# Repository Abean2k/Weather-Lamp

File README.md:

# Weather-Lamp

A lamp with 5 RGB LED's that connects to the weather usign ESP32 to display the "mood" outside. Made for STASIS. 

## Assembly Guide
### Items you need (Besides the PCB and 3D Printed Parts):
2 M3 6mm-12mm screws
2 M4 6mm-12mm screws

First take the base and slide in the oled screen. Keep the wires up like in the picture so that they line up with the cutout in the base. 

Next use the 2 M3 screws to screw the base to the PCB. Make sure to keep the usb on the esp 32 facing the cutout. Also keep LEDs up.

Then prepare the top cover by glueing the the translusent petg crystle to the lip of the top cover usign super glue or hotglue. Be careful while handeling the crystle as 1 layered 3d prints are fragile. 

Finally, take the top cover with the crystle on it and screw it into the base with the 2 M4 screws. 

That's it, now just ubload firmware and you are good to go :)

## Design:
I wanted this lamp to be small and unique. This is why I choose to make a more difficult, but better looking crystal/geode lamp. I also wanted to have an OLED to convey the exact temperature which was something the rgb lamp could not. For the base of the design I tried to keep it as minimalist as possible, which led to it essentially wrapping around the circular pcb, with a flat front surface for the oled. 

The bottom two peices; bottom case, and top cover will be printed using pla in gray or black and the crystle will be a vase mode print with clear/transulcent PETG. PCB will be assembled by hand.  

## PCB:
I made my 2 layered pcb for this project on kicad. I choose to use a pcb for this project in order to keep the lamp internals neat and professional looking. The design of this pcb keeps the LEDs in a circle with one in the center and the microcontroller and capacitor on the back side. For the OLED a header allows me to connect and solder the wires to the pcb to the OLED while allowing the OLED to be in a different direction from my LEDs and microcontroller.

### Schematic

### PCB Layout

## Firmware:
The firmware for this project was made in arduino in c++. It tells the microcontroller how to fetch data from OpenWeather and use the temperature and weather code data from that to light up the LEDs and display the temperature on the OLED in fahrenheit. 

#### How to Upload: Plug in usb through the large opening and upload through arudino ide.

## BOM:

Note: For items with more than my reqired amount it is due to min order limits.

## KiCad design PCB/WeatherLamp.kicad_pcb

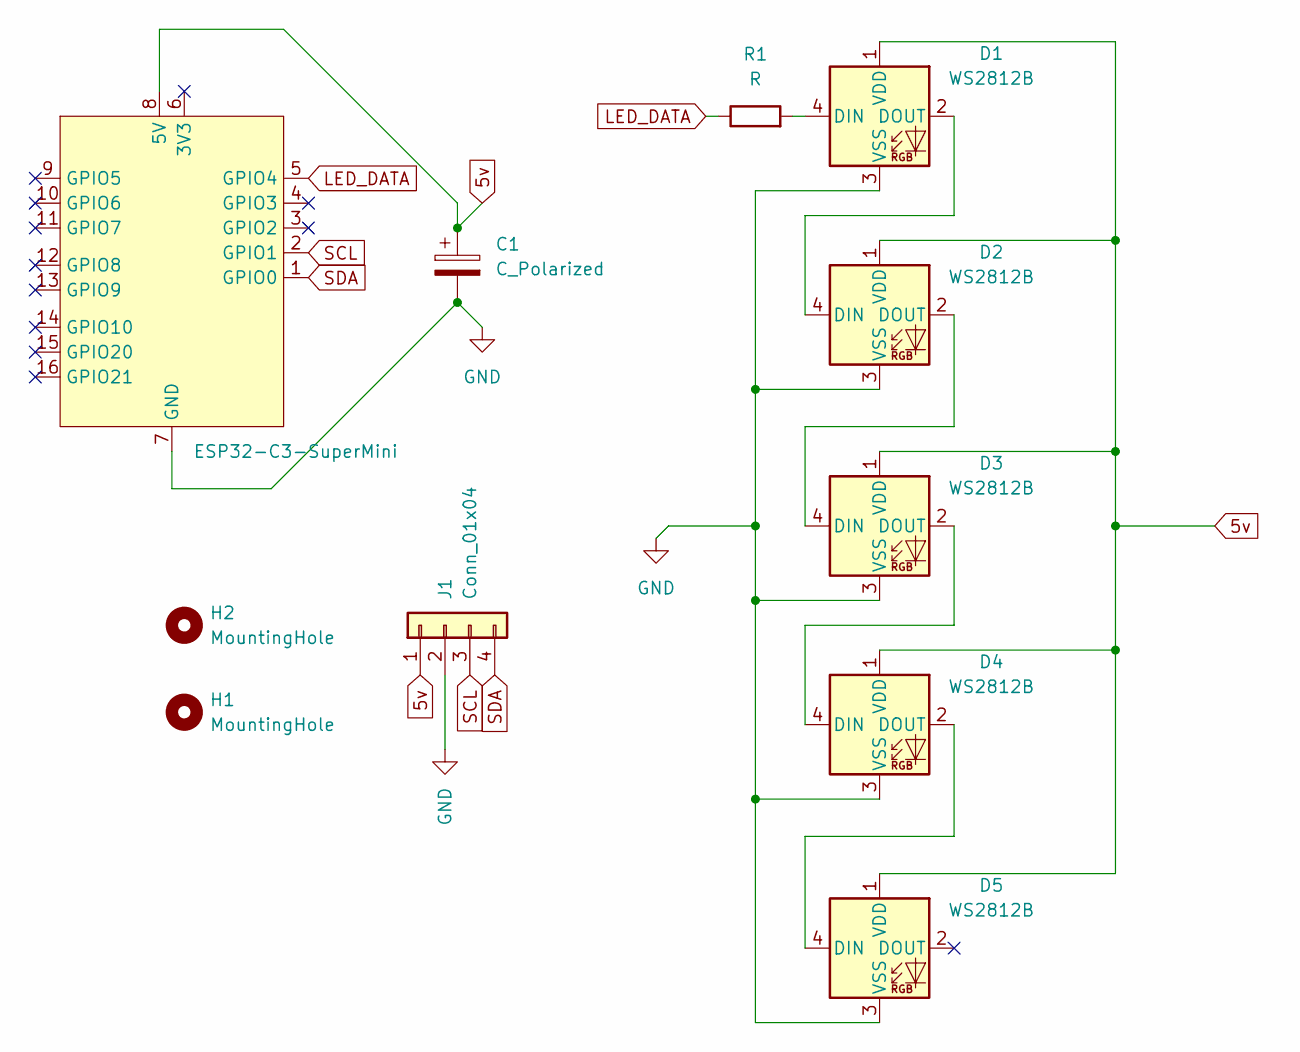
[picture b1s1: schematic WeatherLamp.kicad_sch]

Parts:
C1: C_Polarized; CP_Elec_6.3x5.4
D1, D2, D3, D4, D5: WS2812B; LED_WS2812B_PLCC4_5.0x5.0mm_P3.2mm
H1, H2: MountingHole; MountingHole_3.2mm_M3
J1: Conn_01x04; PinHeader_1x04_P2.54mm_Vertical
R1: R; R_1206_3216Metric_Pad1.30x1.75mm_HandSolder
U1: ESP32-C3-SuperMini

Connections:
5v: C1.1, D1.1 (VDD), D2.1 (VDD), D3.1 (VDD), D4.1 (VDD), D5.1 (VDD), J1.1, U1.8 (5V)
GND: C1.2, D1.3 (VSS), D2.3 (VSS), D3.3 (VSS), D4.3 (VSS), D5.3 (VSS), J1.2, U1.7 (GND)
LED_DATA: R1.1, U1.5 (GPIO4)
unnamed: D1.4 (DIN), R1.2
unnamed: D1.2 (DOUT), D2.4 (DIN)
unnamed: D2.2 (DOUT), D3.4 (DIN)
unnamed: D3.2 (DOUT), D4.4 (DIN)
unnamed: D4.2 (DOUT), D5.4 (DIN)
SCL: J1.3, U1.2 (GPIO1)
SDA: J1.4, U1.1 (GPIO0)

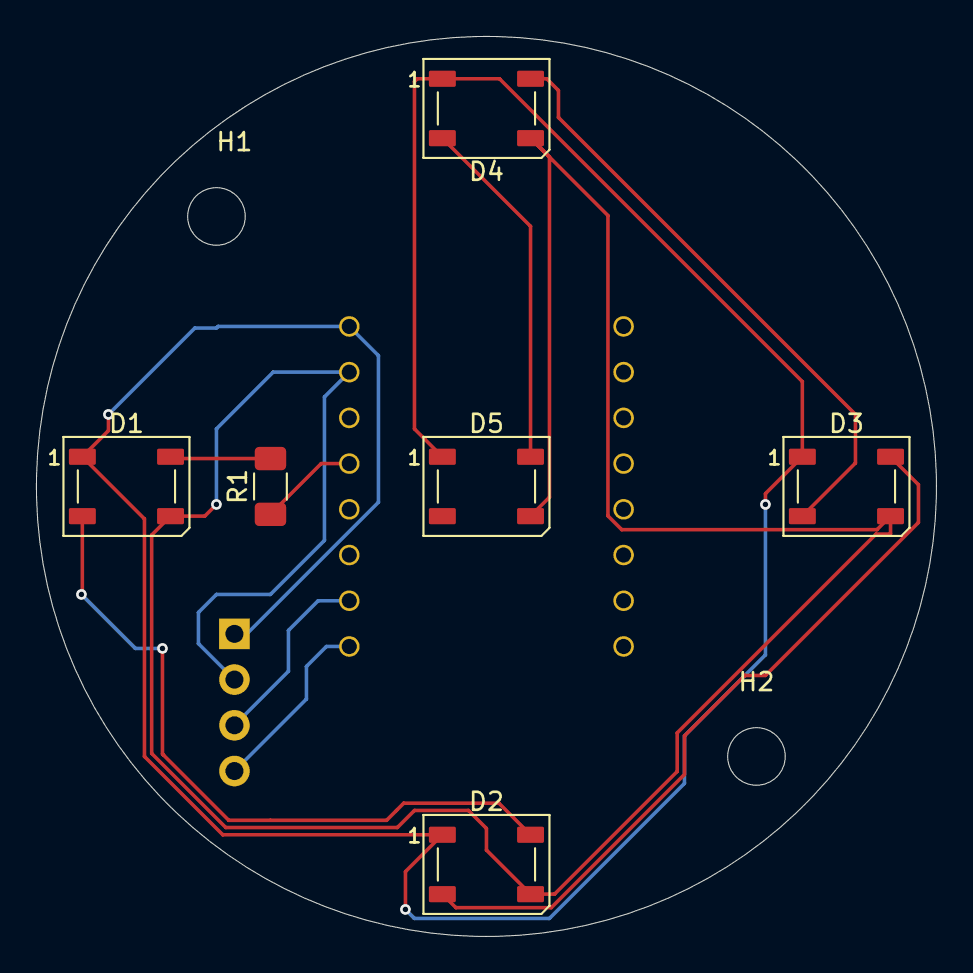
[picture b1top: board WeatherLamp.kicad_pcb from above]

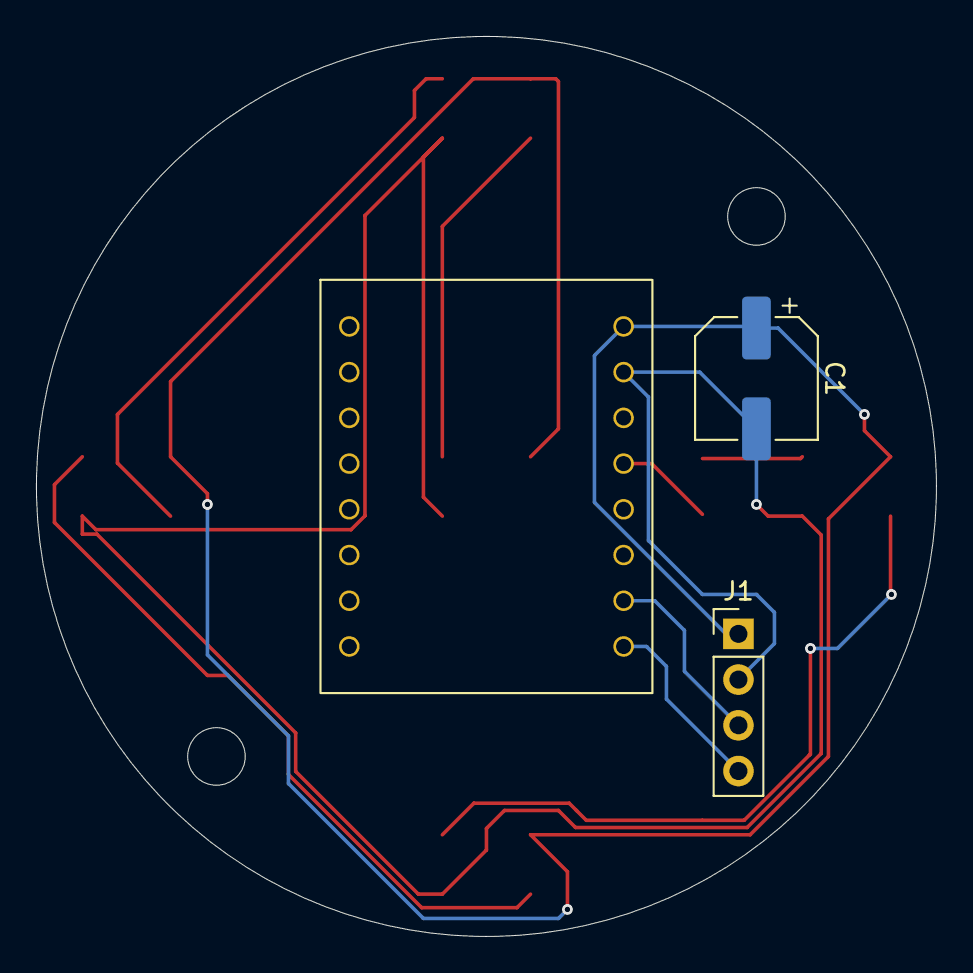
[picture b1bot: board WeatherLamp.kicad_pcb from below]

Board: 2 copper layers, 50.0 x 50.0 mm, 11 parts (3 on the bottom side), 10 nets.

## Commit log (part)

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2026-04-18 Most Files Added
2026-04-18 Added parts to print
2026-04-18 Expand README with project details and images
    Added detailed sections on design, PCB, firmware, and BOM.
2026-04-24 Enhance README with assembly guide and project details
    Added assembly guide and details for the WeatherLamp project, including required items and assembly steps. Updated project description for clarity.
2026-06-17 Add image to README for Weather-Lamp project
    Added an additional image to the README for better visualization.
2026-06-17 Build Commit
2026-06-20 Update README with assembly instructions corrections
    Correct typos and improve clarity in assembly instructions.
